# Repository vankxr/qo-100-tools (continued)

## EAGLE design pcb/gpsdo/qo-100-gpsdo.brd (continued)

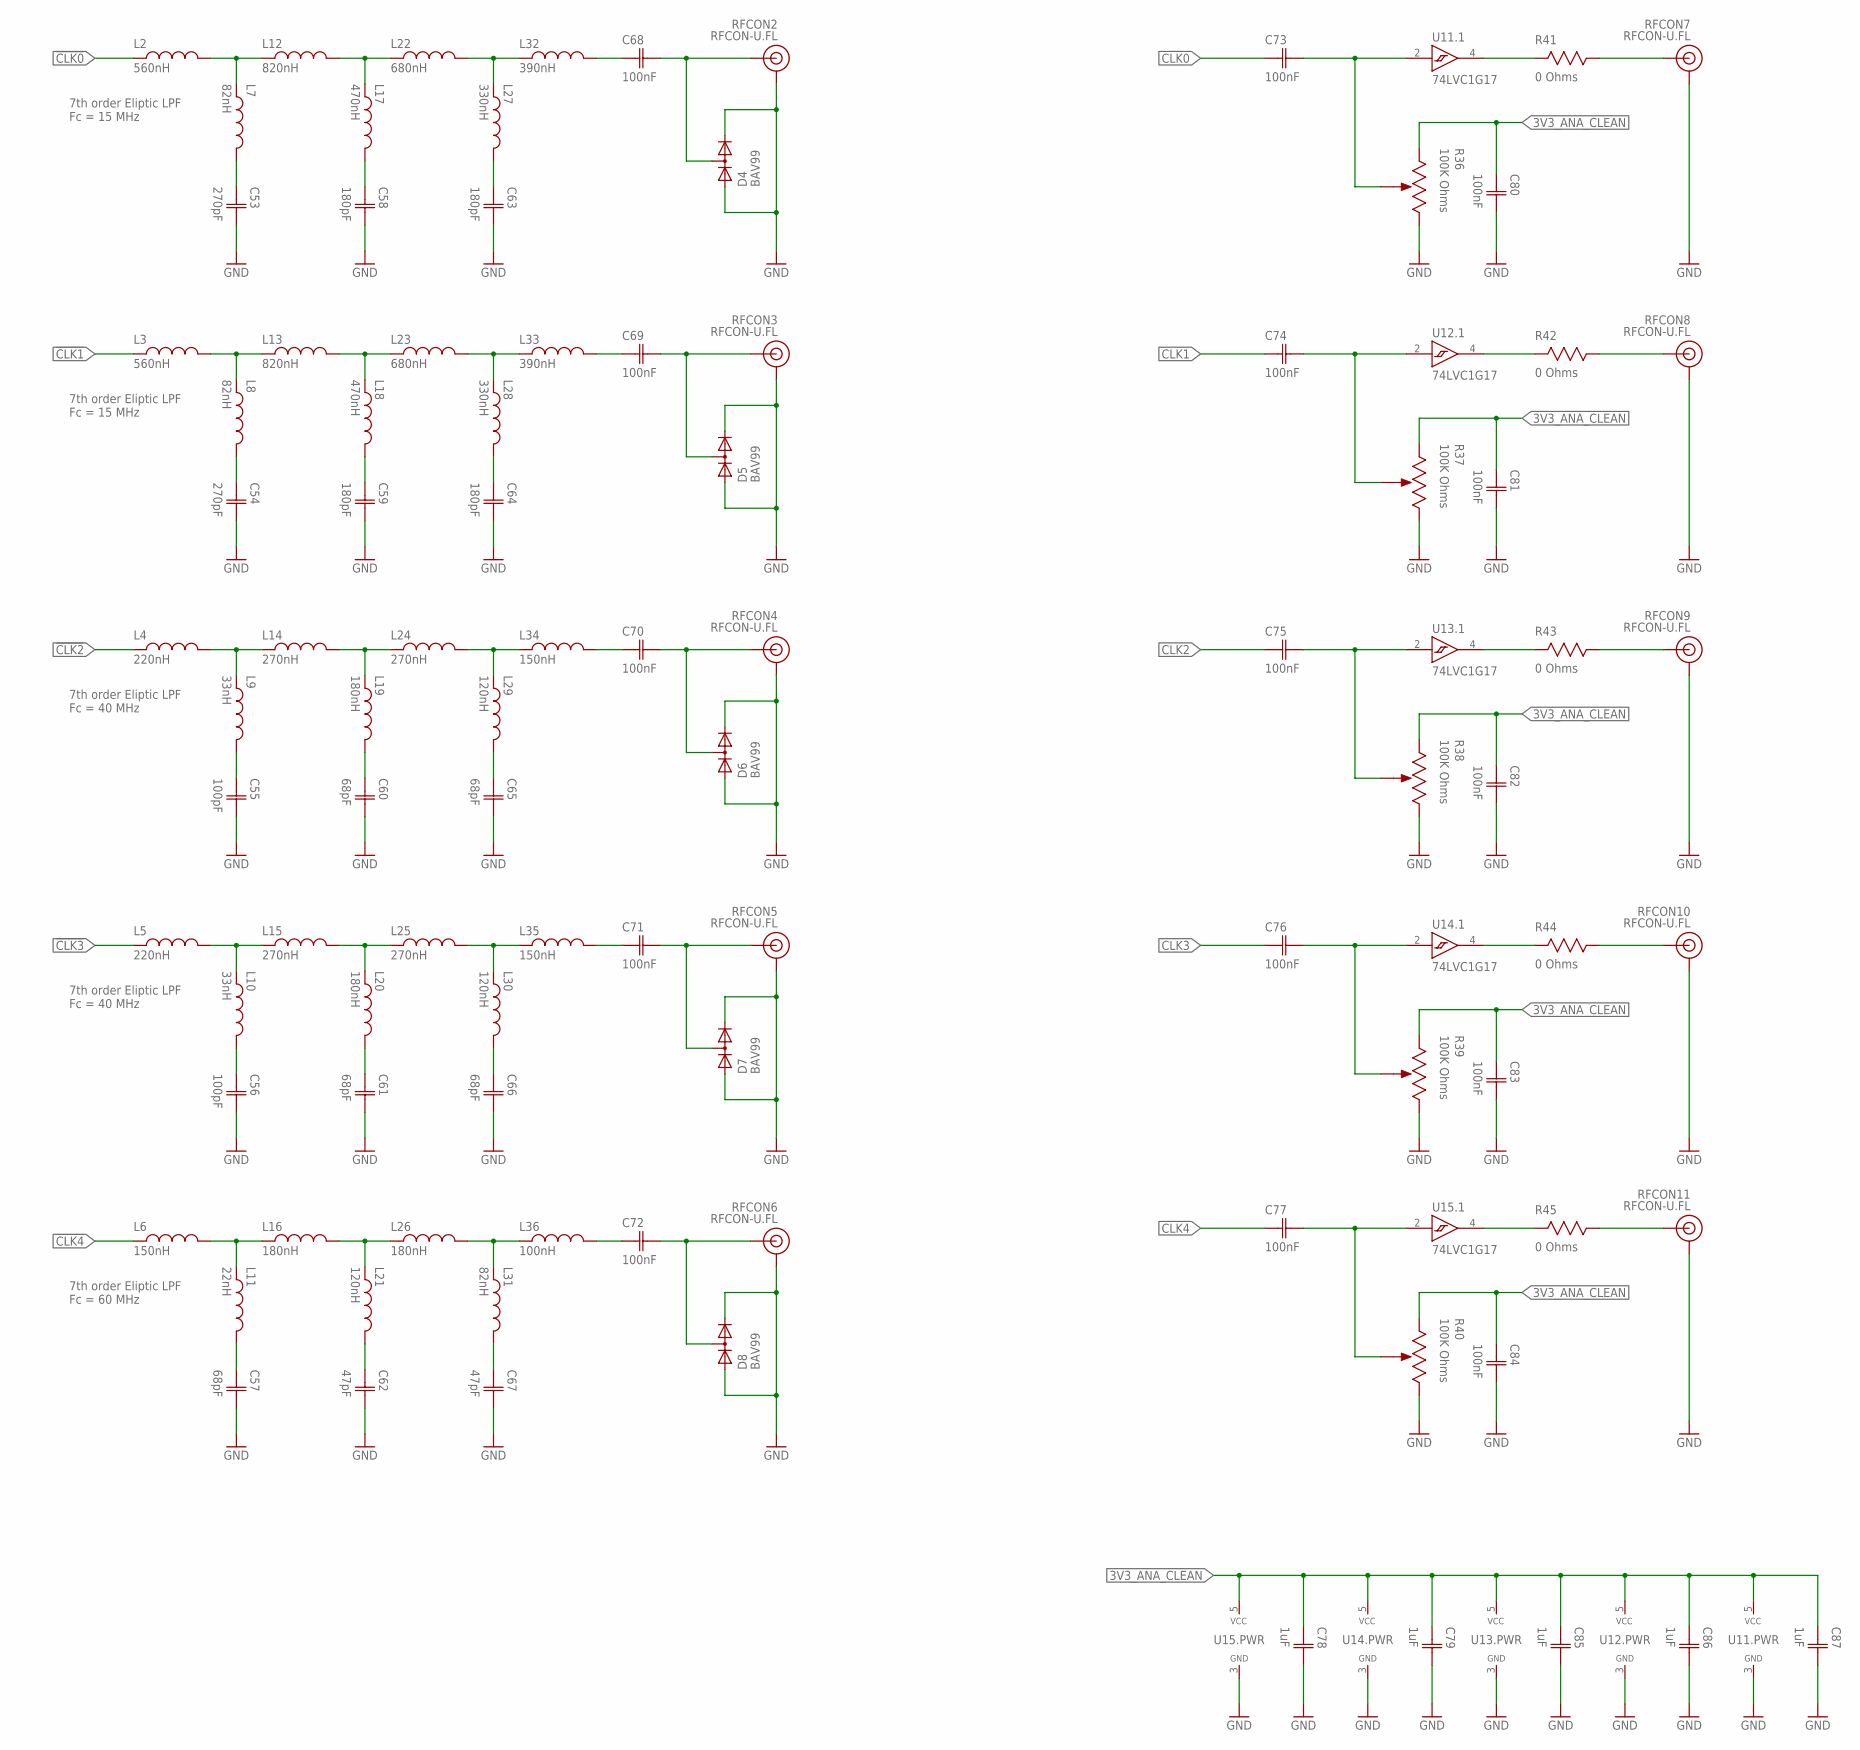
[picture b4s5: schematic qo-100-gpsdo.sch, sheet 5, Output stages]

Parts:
C53, C54: 270pF; CAP0402
C55, C56: 100pF; CAP0402
C57, C60, C61, C65, C66: 68pF; CAP0402
C58, C59, C63, C64: 180pF; CAP0402
C62, C67: 47pF; CAP0402
C68, C69, C70, C71, C72, C73, C74, C75, C76, C77, C80, C81, C82, C83, C84: 100nF; CAP0402
C78, C79, C85, C86, C87: 1uF; CAP0402
D4, D5, D6, D7, D8: BAV99; SOT23
L2, L3: 560nH; IND0402
L4, L5: 220nH; IND0402
L6, L34, L35: 150nH; IND0402
L7, L8, L31: 82nH; IND0402
L9, L10: 33nH; IND0402
L11: 22nH; IND0402
L12, L13: 820nH; IND0402
L14, L15, L24, L25: 270nH; IND0402
L16, L19, L20, L26: 180nH; IND0402
L17, L18: 470nH; IND0402
L21, L29, L30: 120nH; IND0402
L22, L23: 680nH; IND0402
L27, L28: 330nH; IND0402
L32, L33: 390nH; IND0402
L36: 100nH; IND0402
R36, R37, R38, R39, R40: 100K Ohms; POT3MM
R41, R42, R43, R44, R45: 0 Ohms; RES0402
RFCON2, RFCON3, RFCON4, RFCON5, RFCON6, RFCON7, RFCON8, RFCON9, RFCON10, RFCON11: RFCON-U.FL; U.FL
U11, U12, U13, U14, U15: 74LVC1G17; SC70-5

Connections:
3V3_ANA_CLEAN: C78.1 (C1), C79.1 (C1), C80.1 (C1), C81.1 (C1), C82.1 (C1), C83.1 (C1), C84.1 (C1), C85.1 (C1), C86.1 (C1), C87.1 (C1), R36.1 (CCW), R37.1 (CCW), R38.1 (CCW), R39.1 (CCW), R40.1 (CCW), U11.5 (VCC), U12.5 (VCC), U13.5 (VCC), U14.5 (VCC), U15.5 (VCC); also elsewhere on the board
!CLK0: L2.1; also elsewhere on the board
!CLK1: L3.1; also elsewhere on the board
!CLK2: L4.1; also elsewhere on the board
!CLK3: L5.1; also elsewhere on the board
!CLK4: L6.1; also elsewhere on the board
CLK0: C73.1 (C1); also elsewhere on the board
CLK1: C74.1 (C1); also elsewhere on the board
CLK2: C75.1 (C1); also elsewhere on the board
CLK3: C76.1 (C1); also elsewhere on the board
CLK4: C77.1 (C1); also elsewhere on the board
GND: C53.2 (C2), C54.2 (C2), C55.2 (C2), C56.2 (C2), C57.2 (C2), C58.2 (C2), C59.2 (C2), C60.2 (C2), C61.2 (C2), C62.2 (C2), C63.2 (C2), C64.2 (C2), C65.2 (C2), C66.2 (C2), C67.2 (C2), C78.2 (C2), C79.2 (C2), C80.2 (C2), C81.2 (C2), C82.2 (C2), C83.2 (C2), C84.2 (C2), C85.2 (C2), C86.2 (C2), C87.2 (C2), D4.1 (A), D4.2 (C), D5.1 (A), D5.2 (C), D6.1 (A), D6.2 (C), D7.1 (A), D7.2 (C), D8.1 (A), D8.2 (C), R36.3 (CW), R37.3 (CW), R38.3 (CW), R39.3 (CW), R40.3 (CW), RFCON2.P$1 (GND), RFCON2.P$2 (GND), RFCON3.P$1 (GND), RFCON3.P$2 (GND), RFCON4.P$1 (GND), RFCON4.P$2 (GND), RFCON5.P$1 (GND), RFCON5.P$2 (GND), RFCON6.P$1 (GND), RFCON6.P$2 (GND), RFCON7.P$1 (GND), RFCON7.P$2 (GND), RFCON8.P$1 (GND), RFCON8.P$2 (GND), RFCON9.P$1 (GND), RFCON9.P$2 (GND), RFCON10.P$1 (GND), RFCON10.P$2 (GND), RFCON11.P$1 (GND), RFCON11.P$2 (GND), U11.3 (GND), U12.3 (GND), U13.3 (GND), U14.3 (GND), U15.3 (GND); also elsewhere on the board
unnamed: C53.1 (C1), L7.2
unnamed: C58.1 (C1), L17.2
unnamed: C63.1 (C1), L27.2
unnamed: C68.1 (C1), L32.2
unnamed: L3.2, L8.1, L13.1
unnamed: L13.2, L18.1, L23.1
unnamed: R45.1, RFCON11.P$3 (SIGNAL)
unnamed: C69.2 (C2), D5.3 (MID), RFCON3.P$3 (SIGNAL)
unnamed: C77.2 (C2), R40.2 (WIPER), U15.2 (A)
unnamed: R45.2, U15.4 (Y)
unnamed: R44.1, RFCON10.P$3 (SIGNAL)
unnamed: R44.2, U14.4 (Y)
unnamed: C76.2 (C2), R39.2 (WIPER), U14.2 (A)
unnamed: L23.2, L28.1, L33.1
unnamed: C54.1 (C1), L8.2
unnamed: C59.1 (C1), L18.2
unnamed: C64.1 (C1), L28.2
unnamed: C69.1 (C1), L33.2
unnamed: L2.2, L7.1, L12.1
unnamed: L12.2, L17.1, L22.1
unnamed: C68.2 (C2), D4.3 (MID), RFCON2.P$3 (SIGNAL)
unnamed: L22.2, L27.1, L32.1
unnamed: L4.2, L9.1, L14.1
unnamed: L14.2, L19.1, L24.1
unnamed: C70.2 (C2), D6.3 (MID), RFCON4.P$3 (SIGNAL)
unnamed: L24.2, L29.1, L34.1
unnamed: C55.1 (C1), L9.2
unnamed: C60.1 (C1), L19.2
unnamed: C65.1 (C1), L29.2
unnamed: C70.1 (C1), L34.2
unnamed: L5.2, L10.1, L15.1
unnamed: L15.2, L20.1, L25.1
unnamed: C71.2 (C2), D7.3 (MID), RFCON5.P$3 (SIGNAL)
unnamed: L25.2, L30.1, L35.1
unnamed: C56.1 (C1), L10.2
unnamed: C61.1 (C1), L20.2
unnamed: C66.1 (C1), L30.2
unnamed: C71.1 (C1), L35.2
unnamed: L6.2, L11.1, L16.1
unnamed: L16.2, L21.1, L26.1
unnamed: C72.2 (C2), D8.3 (MID), RFCON6.P$3 (SIGNAL)
unnamed: L26.2, L31.1, L36.1
unnamed: C57.1 (C1), L11.2
unnamed: C62.1 (C1), L21.2
unnamed: C67.1 (C1), L31.2
unnamed: C72.1 (C1), L36.2
unnamed: R43.1, RFCON9.P$3 (SIGNAL)
unnamed: R43.2, U13.4 (Y)
unnamed: C75.2 (C2), R38.2 (WIPER), U13.2 (A)
unnamed: R42.1, RFCON8.P$3 (SIGNAL)
unnamed: R42.2, U12.4 (Y)
unnamed: C74.2 (C2), R37.2 (WIPER), U12.2 (A)
unnamed: R41.1, RFCON7.P$3 (SIGNAL)
unnamed: R41.2, U11.4 (Y)
unnamed: C73.2 (C2), R36.2 (WIPER), U11.2 (A)

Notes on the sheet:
7th order Eliptic LPF Fc = 15 MHz
7th order Eliptic LPF Fc = 40 MHz
7th order Eliptic LPF Fc = 60 MHz

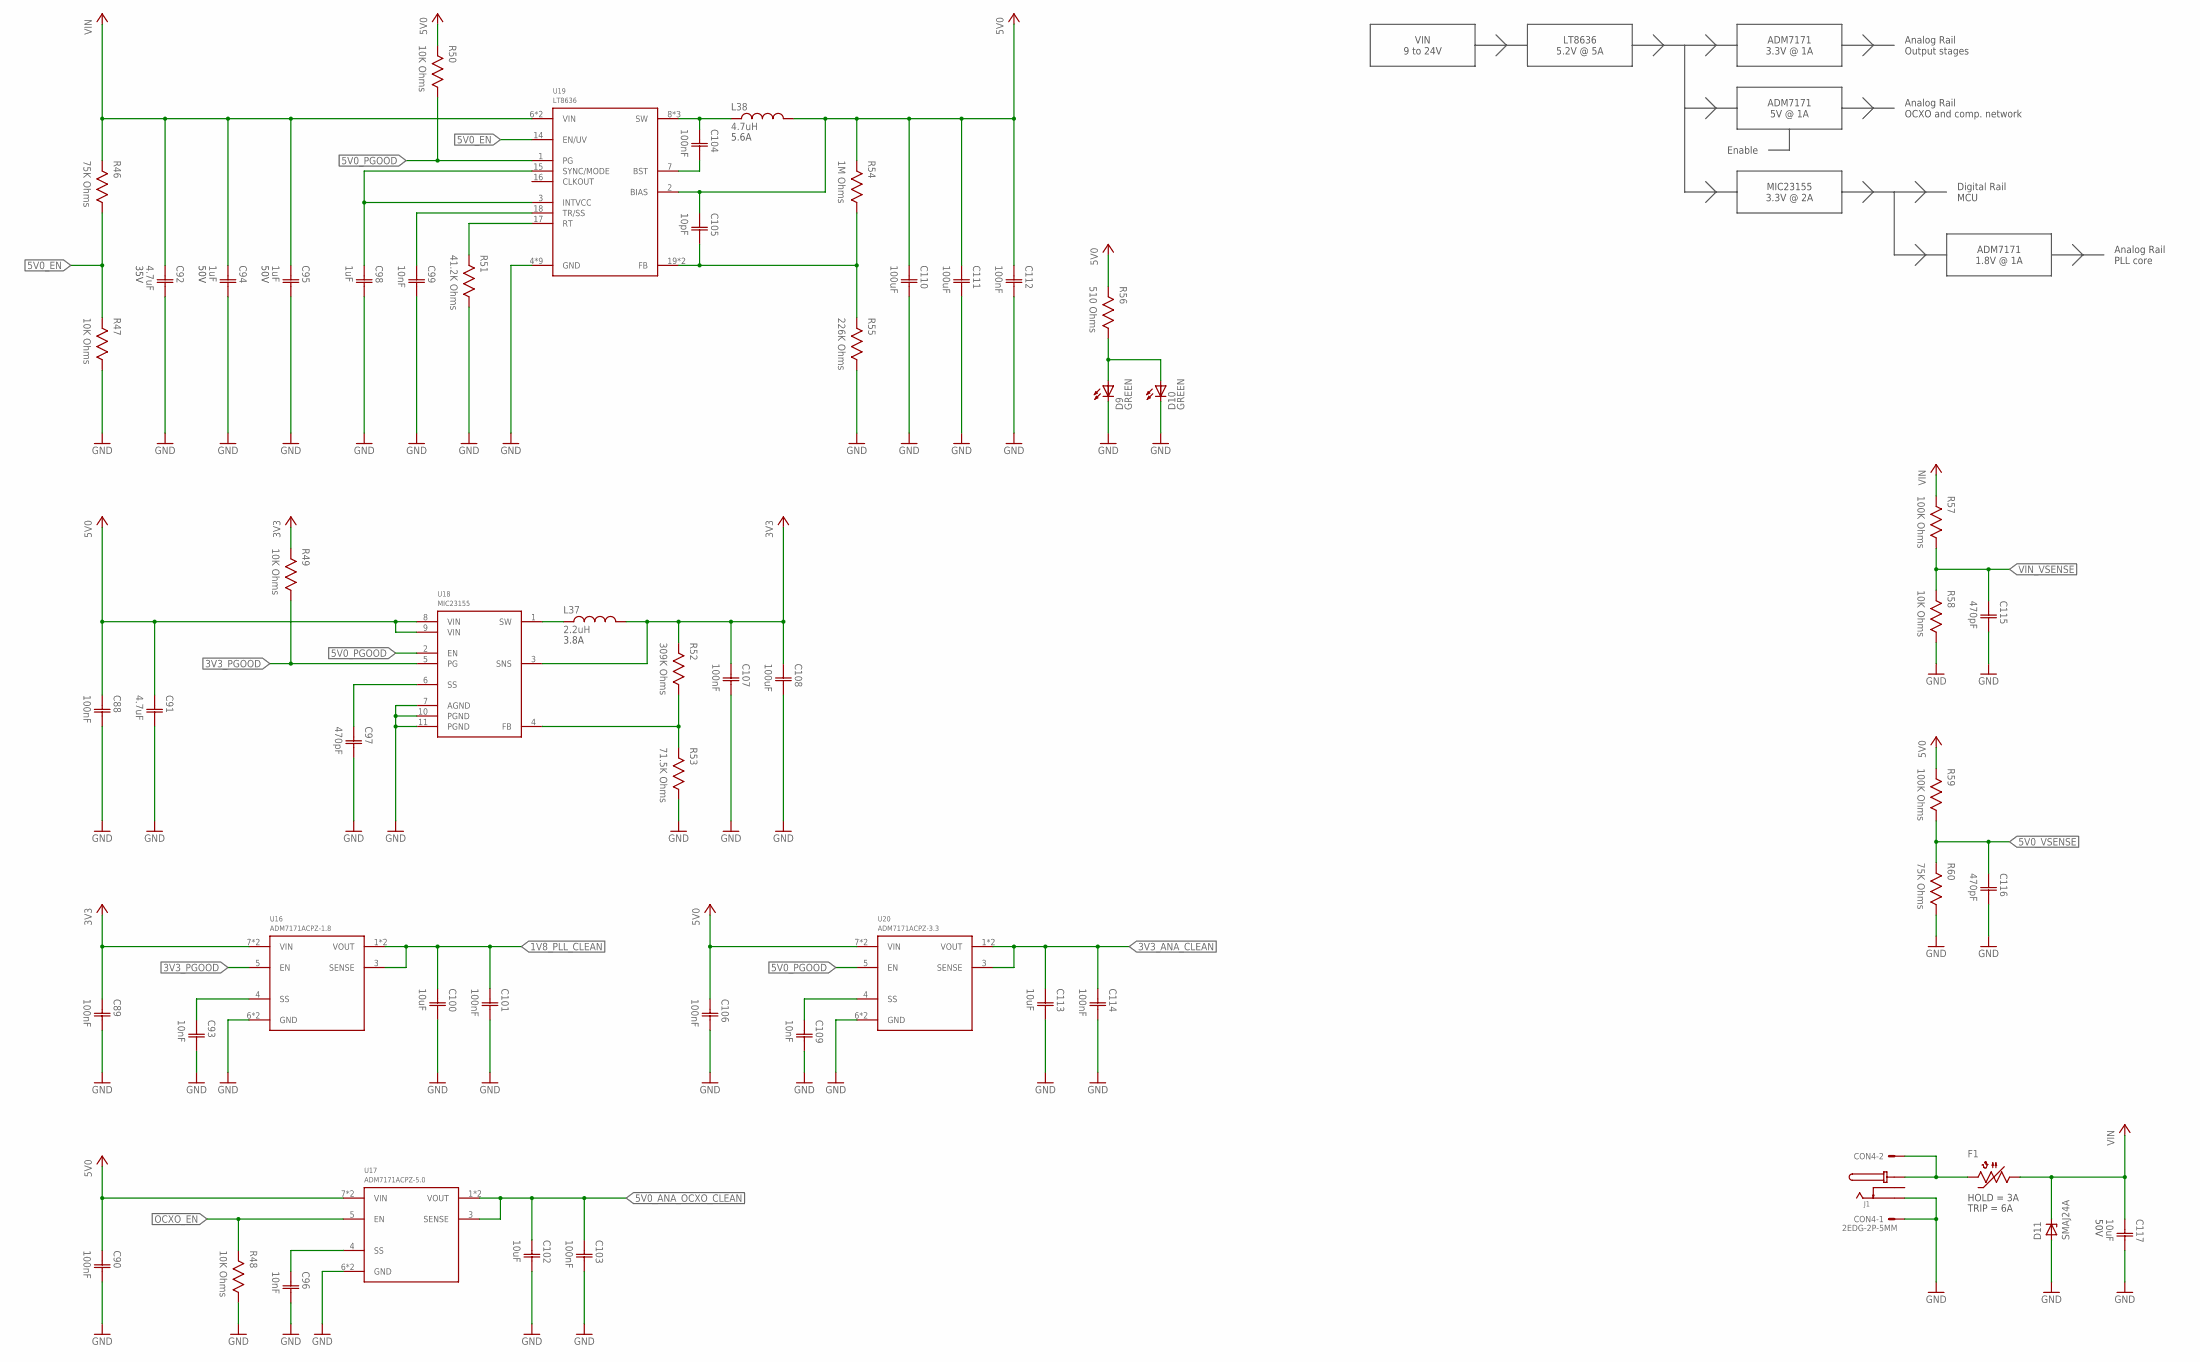
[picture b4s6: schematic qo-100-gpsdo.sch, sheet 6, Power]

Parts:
C88, C89, C90, C101, C103, C104, C106, C107, C112, C114: 100nF; CAP0402
C91: 4.7uF; CAP0603
C92: 4.7uF; CAP0603; VOLTAGE 35V
C93, C96, C99, C109: 10nF; CAP0402
C94, C95: 1uF; CAP0603; VOLTAGE 50V
C97, C115, C116: 470pF; CAP0402
C98: 1uF; CAP0402
C100, C102, C113: 10uF; CAP0603
C105: 10pF; CAP0402
C108, C110, C111: 100uF; CAP1206
C117: 10uF; CAP1206; VOLTAGE 50V
CON4: 2EDG-2P-5MM
D9: LED0603; 0603
D10: LEDTH3MM; LED_3MM
D11: SMAJ24A; DO214AC
F1: 2.6A Hold; 1206
J1: DCJACK; DC-050
L37: 2.2uH; IND3515
L38: 4.7uH; IND0404
R46, R60: 75K Ohms; RES0402
R47, R48, R49, R50, R58: 10K Ohms; RES0402
R51: 41.2K Ohms; RES0402
R52: 309K Ohms; RES0402
R53: 71.5K Ohms; RES0402
R54: 1M Ohms; RES0402
R55: 226K Ohms; RES0402
R56: 510 Ohms; RES0402
R57, R59: 100K Ohms; RES0402
U16: ADM7171ACPZ-1.8; LFCSP8_3X3
U17: ADM7171ACPZ-5.0; LFCSP8_3X3
U18: MIC23155; DFN10
U19: LT8636; QFN20_ASYM_3X4_CORNER
U20: ADM7171ACPZ-3.3; LFCSP8_3X3

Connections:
1V8_PLL_CLEAN: C100.1 (C1), C101.1 (C1), U16.1 (VOUT), U16.2 (VOUT), U16.3 (SENSE); also elsewhere on the board
3V3: C89.1 (C1), C107.1 (C1), C108.1 (C1), L37.2, R49.2, R52.2, U16.7 (VIN), U16.8 (VIN), U18.3 (SNS); also elsewhere on the board
3V3_ANA_CLEAN: C113.1 (C1), C114.1 (C1), U20.1 (VOUT), U20.2 (VOUT), U20.3 (SENSE); also elsewhere on the board
3V3_FB: R52.1, R53.2, U18.4 (FB)
3V3_PGOOD: R49.1, U16.5 (EN), U18.5 (PG); also elsewhere on the board
3V3_SS: C97.1 (C1), U18.6 (SS)
3V3_SW: L37.1, U18.1 (SW)
5V0: C88.1 (C1), C90.1 (C1), C91.1 (C1), C105.1 (C1), C106.1 (C1), C110.1 (C1), C111.1 (C1), C112.1 (C1), L38.2, R50.2, R54.2, R56.2, R59.2, U17.7 (VIN), U17.8 (VIN), U18.8 (VIN), U18.9 (VIN), U19.2 (BIAS), U20.7 (VIN), U20.8 (VIN); also elsewhere on the board
5V0_ANA_OCXO_CLEAN: C102.1 (C1), C103.1 (C1), U17.1 (VOUT), U17.2 (VOUT), U17.3 (SENSE); also elsewhere on the board
5V0_BST: C104.2 (C2), U19.7 (BST)
5V0_EN: R46.1, R47.2, U19.14 (EN/UV)
5V0_FB: C105.2 (C2), R54.1, R55.2, U19.19 (FB), U19.20 (FB)
5V0_INTVCC: C98.1 (C1), U19.3 (INTVCC), U19.15 (SYNC/MODE)
5V0_PGOOD: R50.1, U18.2 (EN), U19.1 (PG), U20.5 (EN)
5V0_RT: R51.2, U19.17 (RT)
5V0_SS: C99.1 (C1), U19.18 (TR/SS)
5V0_SW: C104.1 (C1), L38.1, U19.8 (SW), U19.9 (SW), U19.10 (SW)
5V0_VSENSE: C116.1 (C1), R59.1, R60.2; also elsewhere on the board
GND: C88.2 (C2), C89.2 (C2), C90.2 (C2), C91.2 (C2), C92.2 (C2), C93.2 (C2), C94.2 (C2), C95.2 (C2), C96.2 (C2), C97.2 (C2), C98.2 (C2), C99.2 (C2), C100.2 (C2), C101.2 (C2), C102.2 (C2), C103.2 (C2), C106.2 (C2), C107.2 (C2), C108.2 (C2), C109.2 (C2), C110.2 (C2), C111.2 (C2), C112.2 (C2), C113.2 (C2), C114.2 (C2), C115.2 (C2), C116.2 (C2), C117.2 (C2), CON4.P$1, D9.C, D10.K (C), D11.A, J1.O, R47.1, R48.1, R51.1, R53.1, R55.1, R58.1, R60.1, U16.6 (GND), U16.9 (GND), U17.6 (GND), U17.9 (GND), U18.7 (AGND), U18.10 (PGND), U18.11 (PGND), U19.4 (GND), U19.5 (GND), U19.12 (GND), U19.13 (GND), U19.21 (GND), U19.M1 (GND), U19.M2 (GND), U19.M3 (GND), U19.M4 (GND), U20.6 (GND), U20.9 (GND); also elsewhere on the board
unnamed: C109.1 (C1), U20.4 (SS)
unnamed: C96.1 (C1), U17.4 (SS)
unnamed: CON4.P$2, F1.2, J1.C, J1.C' (C)
unnamed: C93.1 (C1), U16.4 (SS)
unnamed: D9.A, D10.A, R56.1
OCXO_EN: R48.2, U17.5 (EN); also elsewhere on the board
VIN: C92.1 (C1), C94.1 (C1), C95.1 (C1), C117.1 (C1), D11.C, F1.1, R46.2, R57.2, U19.6 (VIN), U19.11 (VIN)
VIN_VSENSE: C115.1 (C1), R57.1, R58.2; also elsewhere on the board

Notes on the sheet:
VIN 9 to 24V
LT8636 5.2V @ 5A
MIC23155 3.3V @ 2A
Digital Rail MCU
ADM7171 1.8V @ 1A
Analog Rail PLL core
Analog Rail Output stages
ADM7171 5V @ 1A
Analog Rail OCXO and comp. network
ADM7171 3.3V @ 1A
Enable

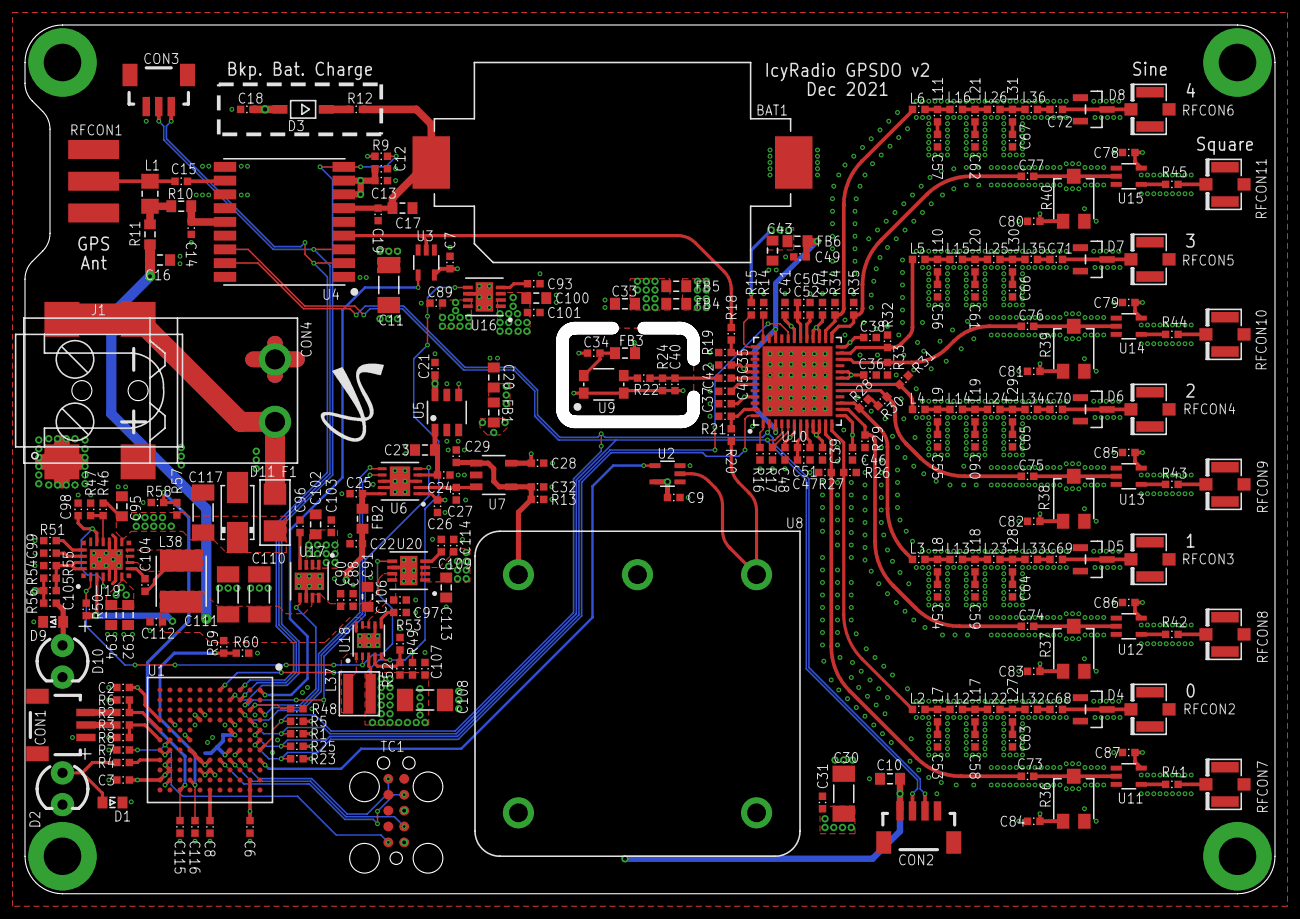
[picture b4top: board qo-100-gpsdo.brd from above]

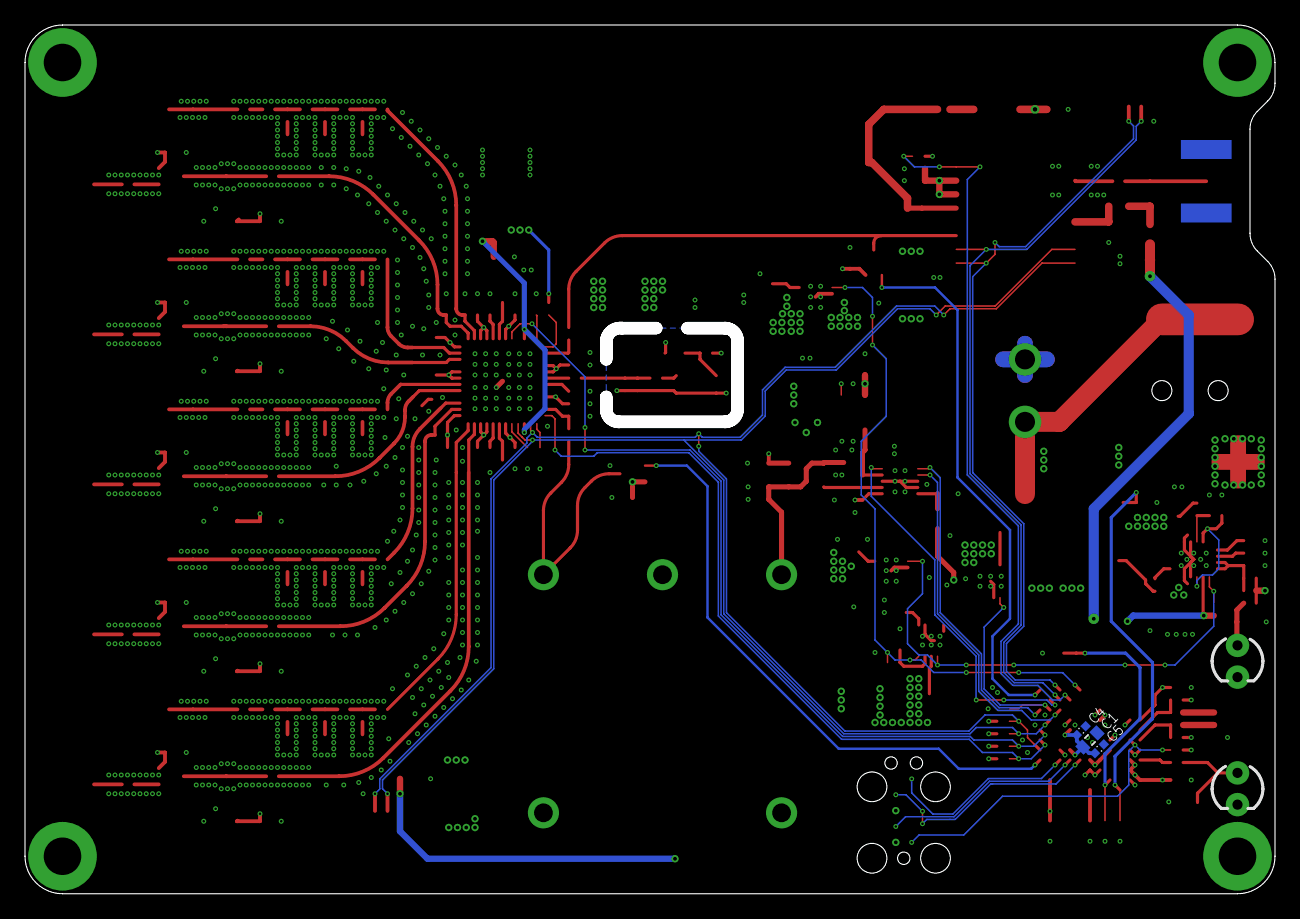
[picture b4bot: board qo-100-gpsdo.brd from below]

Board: 4 copper layers, 100.0 x 69.5 mm, 272 parts (3 on the bottom side), 145 nets.

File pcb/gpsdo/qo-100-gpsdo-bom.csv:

Comment,Footprint,Designator
0 Ohms,RES0402,"R22, R41, R42, R43, R44, R45"
10 Ohms,RES0603,R10
100 Ohms,RES0402,"R2, R3, R27, R29, R31, R33, R35"
100K Ohms,POT3MM,"R36, R37, R38, R39, R40"
100K Ohms,RES0402,"R57, R59"
100nF,CAP0402,"C2, C3, C4, C5, C6, C7, C9, C12, C13, C14, C18, C19, C24, C25, C27, C29, C31, C32, C42, C45, C68, C69, C70, C71, C72, C73, C74, C75, C76, C77, C80, C81, C82, C83, C84, C88, C89, C90, C101, C103, C104, C106, C107, C112, C114"
100nH,IND0402,L36
100pF,CAP0402,"C55, C56"
100uF,CAP1206,"C11, C30, C108, C110, C111"
10K Ohms,RES0402,"R7, R9, R14, R15, R16, R17, R23, R24, R25, R47, R48, R49, R50, R58"
10nF,CAP0402,"C93, C96, C99, C109"
10pF,CAP0402,"C40, C105"
10uF,CAP0603,"C1, C10, C16, C17, C20, C23, C33, C43, C100, C102, C113"
10uF,CAP1206,C117
10uH,IND0603,FB3
120nH,IND0402,"L21, L29, L30"
150nH,IND0402,"L6, L34, L35"
180nH,IND0402,"L16, L19, L20, L26"
180pF,CAP0402,"C58, C59, C63, C64"
1K Ohms,RES0402,R12
1M Ohms,RES0402,R54
1uF,CAP0402,"C8, C21, C22, C26, C28, C34, C35, C36, C37, C38, C39, C41, C44, C46, C48, C49, C78, C79, C85, C86, C87, C98"
1uF,CAP0603,"C94, C95"
1uH,IND0603,"FB1, FB2, FB4, FB5, FB6"
2.2uH,IND3515,L37
2.6A Hold,1206,F1
220nF,CAP0402,"C47, C50"
220nH,IND0402,"L4, L5"
226K Ohms,RES0402,R55
22nH,IND0402,L11
270 Ohms,RES0402,R21
270nH,IND0402,"L14, L15, L24, L25"
270pF,CAP0402,"C53, C54"
27nH,IND0805,L1
280 Ohms,RES0402,R18
2EDG-2P-5MM,2EDG-2P-5MM,CON4
3.9nF,CAP0402,"C51, C52"
309K Ohms,RES0402,R52
330 Ohms,RES0402,"R4, R19"
330nH,IND0402,"L27, L28"
33nH,IND0402,"L9, L10"
390nH,IND0402,"L32, L33"
3P-SH-SIDE,SH-03-SIDE,CON1
3P-SH-TOP,SH-03-TOP,CON3
4.7K Ohms,RES0402,"R1, R5, R6, R8"
4.7uF,CAP0603,"C91, C92"
4.7uH,IND0404,L38
41.2K Ohms,RES0402,R51
470 Ohms,RES0402,R13
470nH,IND0402,"L17, L18"
470pF,CAP0402,"C97, C115, C116"
47pF,CAP0402,"C15, C62, C67"
49.9 Ohms,RES0402,"R26, R28, R30, R32, R34"
4P-SH-TOP,SH-04-TOP,CON2
510 Ohms,RES0402,"R20, R56"
560nH,IND0402,"L2, L3"
680nH,IND0402,"L22, L23"
68pF,CAP0402,"C57, C60, C61, C65, C66"
71.5K Ohms,RES0402,R53
74LVC1G17,SC70-5,"U2, U3, U11, U12, U13, U14, U15"
75K Ohms,RES0402,"R46, R60"
820nH,IND0402,"L12, L13"
82nH,IND0402,"L7, L8, L31"
AD5541ACPZ,DFN10,U6
AD9544,QFN48_2,U10
ADM7171ACPZ-1.8,LFCSP8_3X3,U16
ADM7171ACPZ-3.3,LFCSP8_3X3,U20
ADM7171ACPZ-5.0,LFCSP8_3X3,U17
B0530W,SOD-123,D3
BAV99,SOT23,"D4, D5, D6, D7, D8"
CR2032,CR2032,BAT1
DCJACK,DC-050,J1
DNP,RES0603,R11
DSB321SDA,TCXO-3225,U9
EFM32GG11B420F2048GL112,BGA112,U1
JS-5MM,JS_5MM,LOGO1
LED0603,603,"D1, D9"
LEDTH3MM,LED_3MM,"D2, D10"
LT8636,QFN20_ASYM_3X4_CORNER,U19
MAX-M8Q,MAX-M8,U4
MCP1501-40,SOT23-6,U5
MCP6V31,SOT23-5,U7
MIC23155,DFN10,U18
OSC5A2B02,OSC5A2B02,U8
RFCON-SMA-EDGE,SMA-EDGE,RFCON1
RFCON-U.FL,U.FL,"RFCON2, RFCON3, RFCON4, RFCON5, RFCON6, RFCON7, RFCON8, RFCON9, RFCON10, RFCON11"
SMAJ24A,DO214AC,D11
TC2050-IDC,TC2050-IDC,TC1

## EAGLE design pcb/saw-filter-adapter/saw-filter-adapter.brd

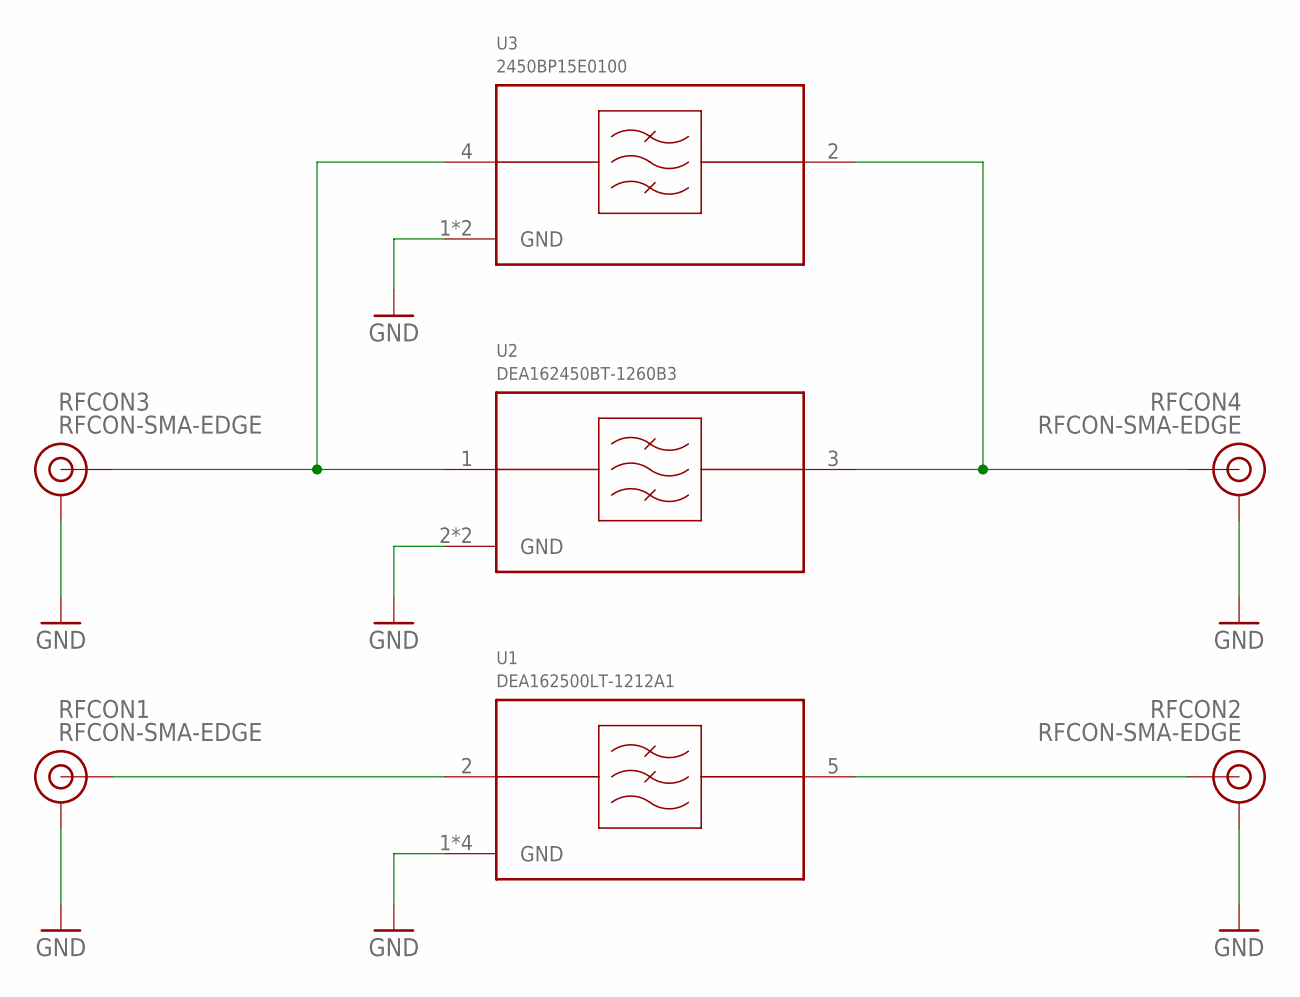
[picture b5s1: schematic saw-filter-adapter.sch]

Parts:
RFCON1, RFCON2, RFCON3, RFCON4: RFCON-SMA-EDGE; SMA-EDGE
U1: DEA162500LT-1212A1
U2: DEA162450BT-1260B3
U3: 2450BP15E0100

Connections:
GND: RFCON1.GND@0 (GND), RFCON1.GND@1 (GND), RFCON1.GND@2 (GND), RFCON1.GND@3 (GND), RFCON2.GND@0 (GND), RFCON2.GND@1 (GND), RFCON2.GND@2 (GND), RFCON2.GND@3 (GND), RFCON3.GND@0 (GND), RFCON3.GND@1 (GND), RFCON3.GND@2 (GND), RFCON3.GND@3 (GND), RFCON4.GND@0 (GND), RFCON4.GND@1 (GND), RFCON4.GND@2 (GND), RFCON4.GND@3 (GND), U1.1 (GND), U1.3 (GND), U1.4 (GND), U1.6 (GND), U2.2 (GND), U2.4 (GND), U3.1 (GND), U3.3 (GND)
unnamed: RFCON1.SIG (SIGNAL), U1.2 (RFIN)
unnamed: RFCON2.SIG (SIGNAL), U1.5 (RFOUT)
unnamed: RFCON4.SIG (SIGNAL), U2.3 (RFOUT), U3.2 (RFOUT)
unnamed: RFCON3.SIG (SIGNAL), U2.1 (RFIN), U3.4 (RFIN)

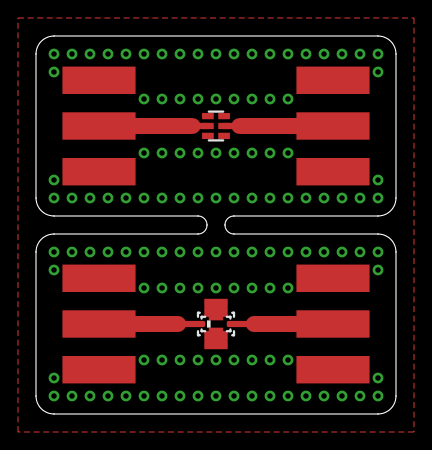
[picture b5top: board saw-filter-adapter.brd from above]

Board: 2 copper layers, 20.0 x 21.0 mm, 7 parts (0 on the bottom side), 5 nets.

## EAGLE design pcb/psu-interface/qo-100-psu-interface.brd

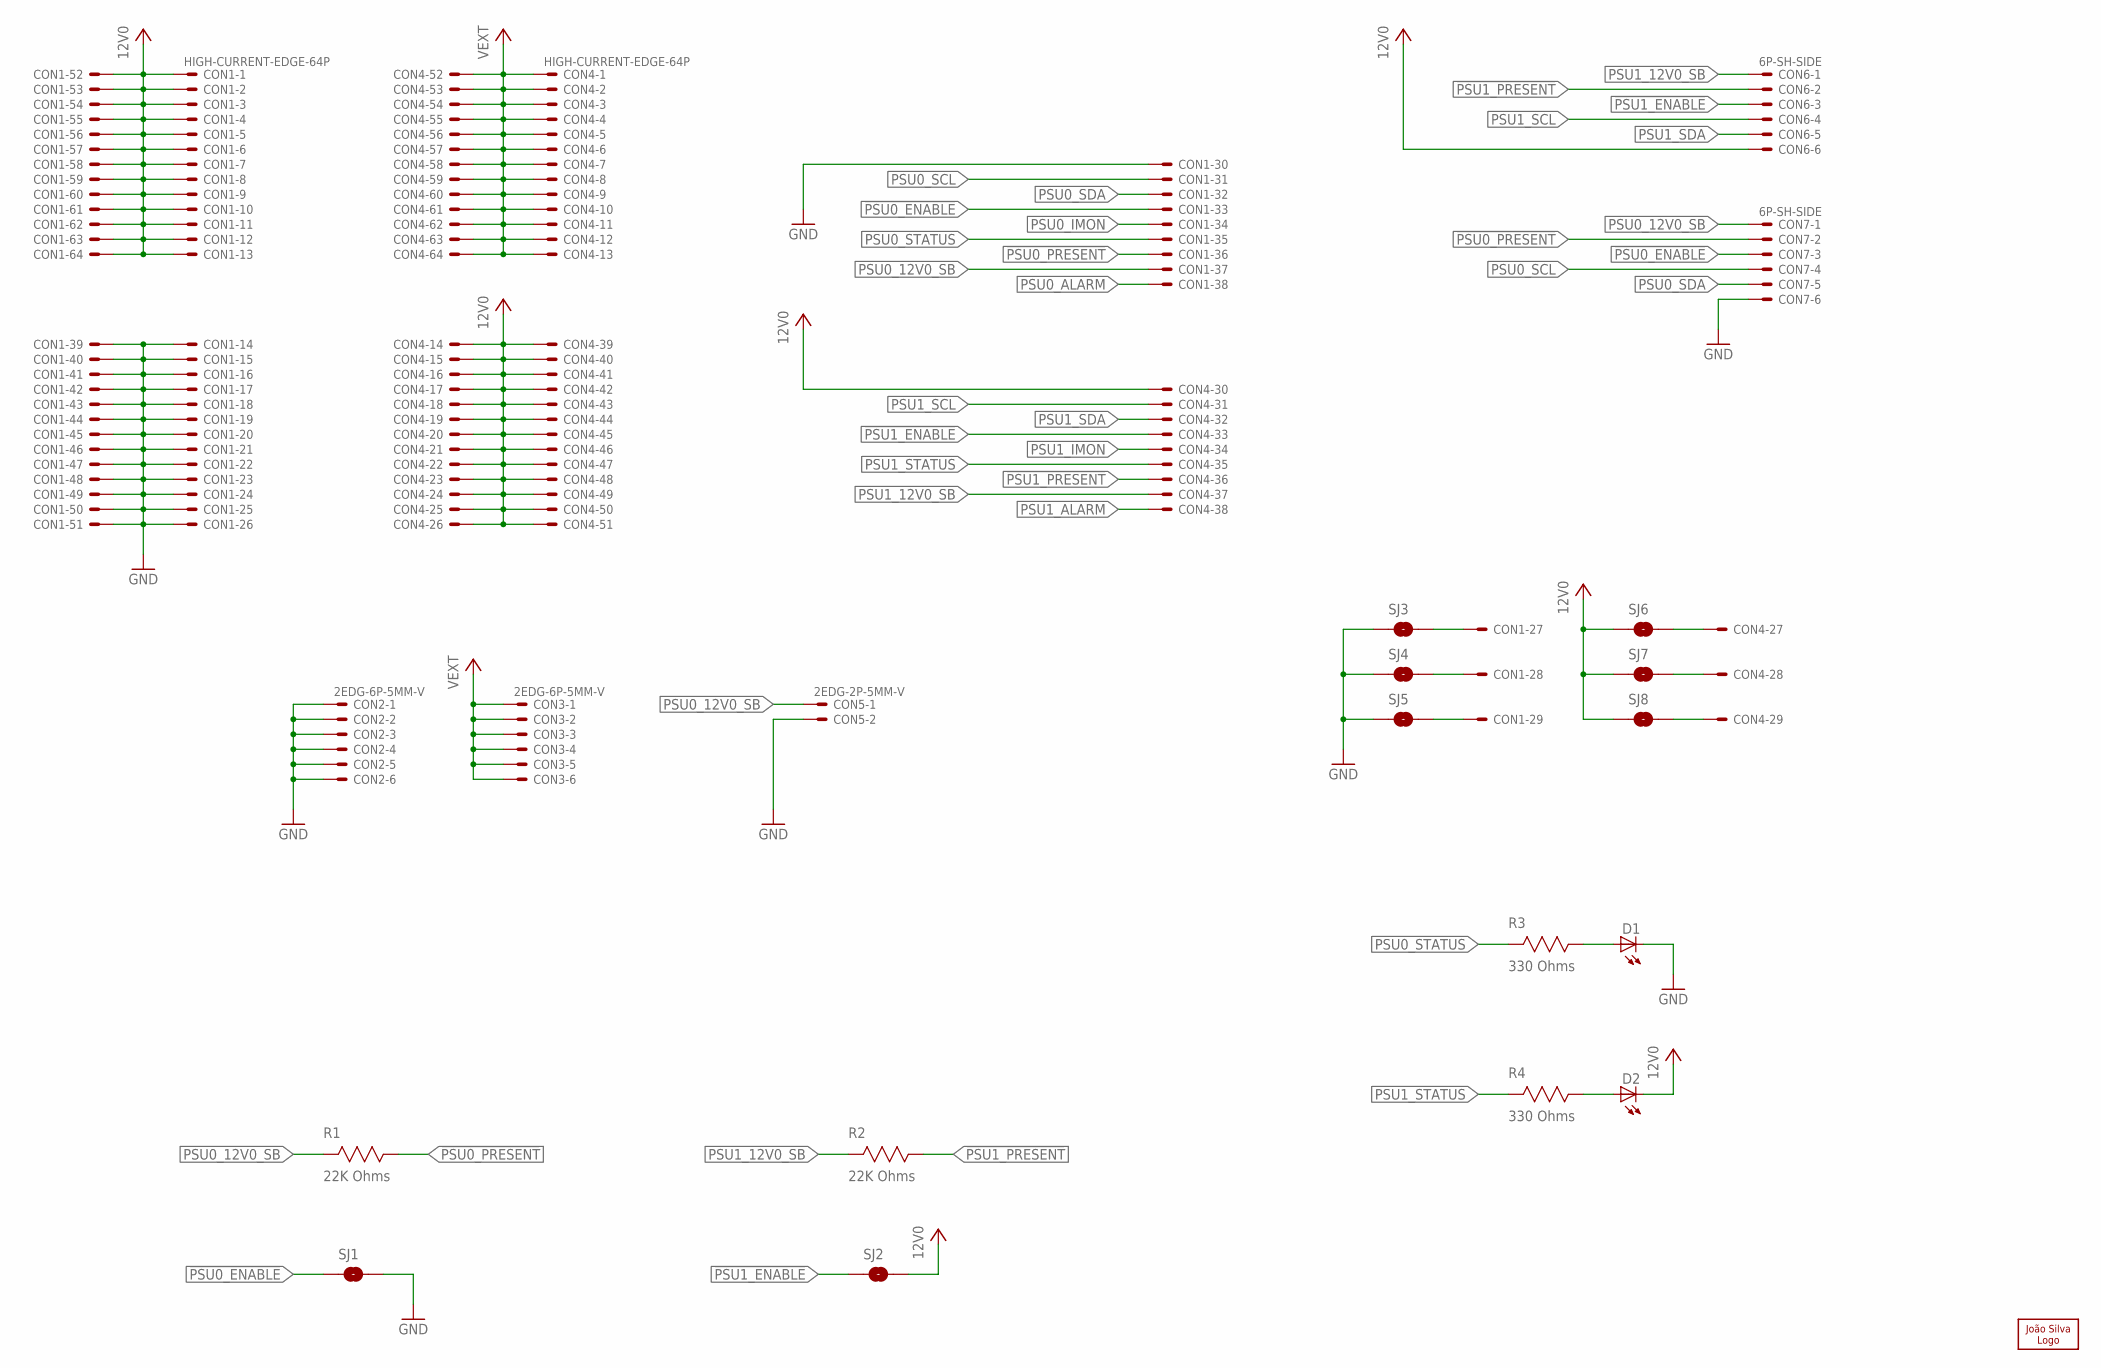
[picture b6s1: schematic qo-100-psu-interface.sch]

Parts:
CON1, CON4: HIGH-CURRENT-EDGE-64P
CON2, CON3: 2EDG-6P-5MM-V
CON5: 2EDG-2P-5MM-V
CON6, CON7: 6P-SH-SIDE; SH-06-SIDE
D1, D2: LED0603; 0603
LOGO1: JS-5MM; JS_5MM
R1, R2: 22K Ohms; RES0603
R3, R4: 330 Ohms; RES0603
SJ1, SJ2, SJ3, SJ4, SJ5, SJ6, SJ7, SJ8: SJS; SJ_S

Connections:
12V0: CON1.1, CON1.2, CON1.3, CON1.4, CON1.5, CON1.6, CON1.7, CON1.8, CON1.9, CON1.10, CON1.11, CON1.12, CON1.13, CON1.52, CON1.53, CON1.54, CON1.55, CON1.56, CON1.57, CON1.58, CON1.59, CON1.60, CON1.61, CON1.62, CON1.63, CON1.64, CON4.14, CON4.15, CON4.16, CON4.17, CON4.18, CON4.19, CON4.20, CON4.21, CON4.22, CON4.23, CON4.24, CON4.25, CON4.26, CON4.30, CON4.39, CON4.40, CON4.41, CON4.42, CON4.43, CON4.44, CON4.45, CON4.46, CON4.47, CON4.48, CON4.49, CON4.50, CON4.51, CON6.6, D2.C, SJ2.2, SJ6.1, SJ7.1, SJ8.1
!PSU0_ENABLE: CON1.33, CON7.3, SJ1.1
!PSU0_PRESENT: CON1.36, CON7.2, R1.1
!PSU1_ENABLE: CON4.33, CON6.3, SJ2.1
!PSU1_PRESENT: CON4.36, CON6.2, R2.1
GND: CON1.14, CON1.15, CON1.16, CON1.17, CON1.18, CON1.19, CON1.20, CON1.21, CON1.22, CON1.23, CON1.24, CON1.25, CON1.26, CON1.30, CON1.39, CON1.40, CON1.41, CON1.42, CON1.43, CON1.44, CON1.45, CON1.46, CON1.47, CON1.48, CON1.49, CON1.50, CON1.51, CON2.P$1, CON2.P$2, CON2.P$3, CON2.P$4, CON2.P$5, CON2.P$6, CON5.P$2, CON7.6, D1.C, SJ1.2, SJ3.1, SJ4.1, SJ5.1
unnamed: CON1.29, SJ5.2
unnamed: CON1.28, SJ4.2
unnamed: CON1.27, SJ3.2
unnamed: CON4.27, SJ6.2
unnamed: CON4.28, SJ7.2
unnamed: CON4.29, SJ8.2
unnamed: D1.A, R3.1
unnamed: D2.A, R4.1
PSU0_12V0_SB: CON1.37, CON5.P$1, CON7.1, R1.2
PSU0_ALARM: CON1.38
PSU0_IMON: CON1.34
PSU0_SCL: CON1.31, CON7.4
PSU0_SDA: CON1.32, CON7.5
PSU0_STATUS: CON1.35, R3.2
PSU1_12V0_SB: CON4.37, CON6.1, R2.2
PSU1_ALARM: CON4.38
PSU1_IMON: CON4.34
PSU1_SCL: CON4.31, CON6.4
PSU1_SDA: CON4.32, CON6.5
PSU1_STATUS: CON4.35, R4.2
VEXT: CON3.P$1, CON3.P$2, CON3.P$3, CON3.P$4, CON3.P$5, CON3.P$6, CON4.1, CON4.2, CON4.3, CON4.4, CON4.5, CON4.6, CON4.7, CON4.8, CON4.9, CON4.10, CON4.11, CON4.12, CON4.13, CON4.52, CON4.53, CON4.54, CON4.55, CON4.56, CON4.57, CON4.58, CON4.59, CON4.60, CON4.61, CON4.62, CON4.63, CON4.64
